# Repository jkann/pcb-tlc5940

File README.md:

# pcb-tlc5940
TLC5940-based multi-function board

Depending on the assembled components this can be one of the following:
(A) 16-channel servo control board
(B) 16-led bar display with idividual led dimming
(C) 5xRGB-led board, each with individial color

In each use case multiple board can be chained with regular 2.54mm jumpers (7x).
RGB-LEDS are spaced 10.0mm so that multiple 50mm x 50mm boards will extend the chain.

29-Apr-2015: Placed an order in iteadstudio.

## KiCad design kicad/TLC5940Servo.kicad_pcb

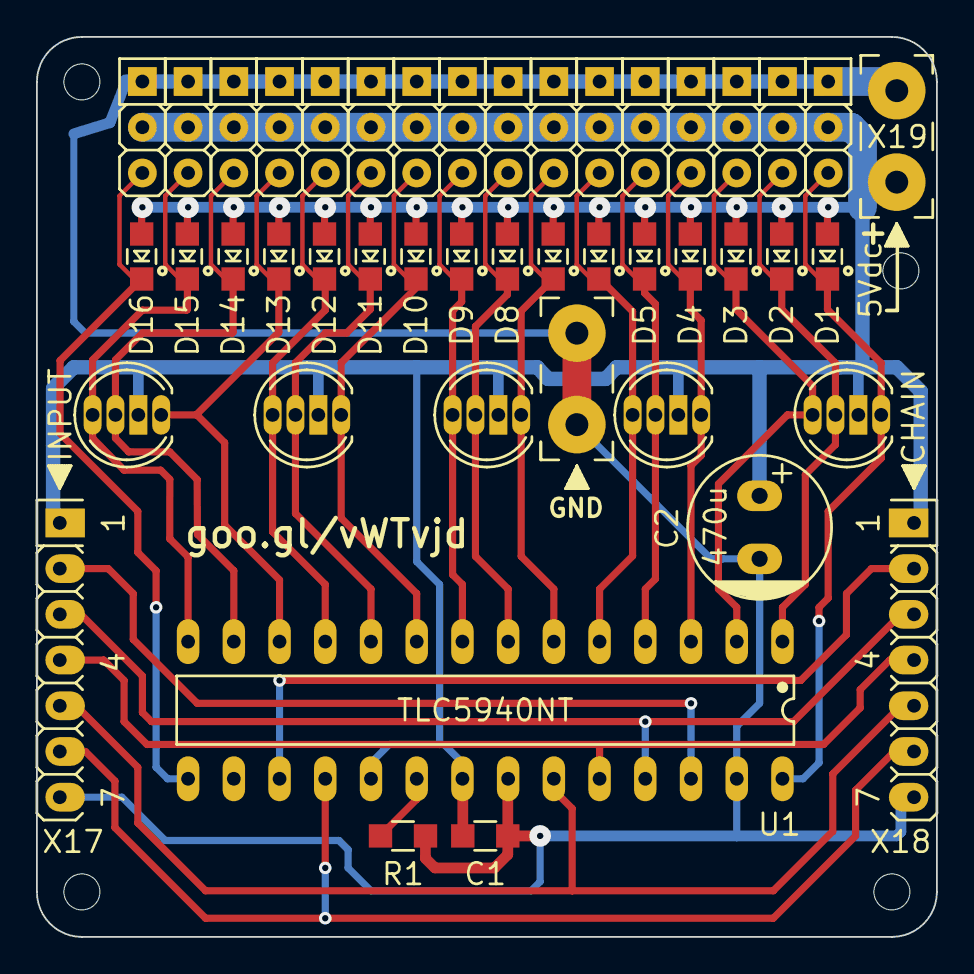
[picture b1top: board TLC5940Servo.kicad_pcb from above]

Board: 2 copper layers, 50.0 x 50.0 mm, 49 parts (0 on the bottom side), 25 nets.

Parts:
2mm, 2mm#2, 2mm#3, 2mm#4: VAL**; JK_NPTH_2mm
C1: 100n; JK_0805_C
C2: 470u; JK_ELKO-d8-r3.5
D1, D2, D3, D4, D5, D6, D7, D8, D9, D10, D11, D12, D13, D14, D15, D16: JK_LED; JK_0805_LED
D17, D18, D19, D20, D21: JK_LED_RGB_CA; JK_LED_5MM_RGB
R1: 2k2; JK_0805_R
U1: TLC5940NT; JK_DIP-28N_N
X1, X2, X3, X4, X5, X6, X7, X8, X9, X10, X11, X12, X13, X14, X15, X16: JK_CONN_3; JK_PH-1x3_SSNM
X17: INPUT; JK_PH-1x7_SR
X18: CHAIN; JK_PH-1x7_SL
X19: 5Vdc; JK_WSP_2x0.75mm2_R
X20: TESTHOOK; JK_WSP_2x0.75mm2_R

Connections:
/BLANK: U1.23, X17.5, X18.5
/GSCLK: U1.18, X17.6, X18.6
/P00: D1.2, D17.1, U1.28, X1.3
/P01: D2.2, D17.3, U1.1, X2.3
/P02: D3.2, D17.4, U1.2, X3.3
/P03: D4.2, D18.1, U1.3, X4.3
/P04: D5.2, D18.3, U1.4, X5.3
/P05: D6.2, D18.4, U1.5, X6.3
/P06: D7.2, D19.1, U1.6, X7.3
/P07: D8.2, D19.3, U1.7, X8.3
/P08: D9.2, D19.4, U1.8, X9.3
/P09: D10.2, D20.1, U1.9, X10.3
/P10: D11.2, D20.3, U1.10, X11.3
/P11: D12.2, D20.4, U1.11, X12.3
/P12: D13.2, D21.1, U1.12, X13.3
/P13: D14.2, D21.3, U1.13, X14.3
/P14: D15.2, D21.4, U1.14, X15.3
/P15: D16.2, U1.15, X16.3
/SCLK: U1.25, X17.3, X18.3
/SIN: U1.26, X17.2
/SOUT: U1.17, X18.2
/XLAT: U1.24, X17.4, X18.4
GND: C1.2, C2.2, R1.1, U1.22, U1.27, X1.1, X2.1, X3.1, X4.1, X5.1, X6.1, X7.1, X8.1, X9.1, X10.1, X11.1, X12.1, X13.1, X14.1, X15.1, X16.1, X17.7, X18.7, X19.2, X20.1, X20.2
unnamed: R1.2, U1.20
VCC: C1.1, C2.1, D1.1, D2.1, D3.1, D4.1, D5.1, D6.1, D7.1, D8.1, D9.1, D10.1, D11.1, D12.1, D13.1, D14.1, D15.1, D16.1, D17.2, D18.2, D19.2, D20.2, D21.2, U1.19, U1.21, X1.2, X2.2, X3.2, X4.2, X5.2, X6.2, X7.2, X8.2, X9.2, X10.2, X11.2, X12.2, X13.2, X14.2, X15.2, X16.2, X17.1, X18.1, X19.1

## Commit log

2015-04-15 First order
